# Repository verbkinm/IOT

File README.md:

<h1>IOTV</h1>
<p>
    Централизированная система управления устройствами. Под устройствами (хостами) могут подразумеваться как автономные устройства на микроконтроллерах, так и отдельные программы на компьютерах.
    Протокол для общения хоста-сервера-клиента написан на Си, так что его легко можно использовать практически на любых микроконтроллерах. На серверной части используется телеграм бот.
</p>

<p>
    Проект состоит из трёх основных частей:
<ol>
    <li>IOTV_Server.</li>
    <li>IOTV_Host.</li>
    <li>IOTV_Client.</li>
</ol>
</p>

<h2>1. IOTV_Server</h2>
<ul>
    <li>Слушает выбранный tcp порт для связи с клиентами (файл настроек).</li>
    <li>Слушает tcp и udp порты для связи с tcp/udp хостами (файл настроек). Так же возможны другие типы подключений, такие как com-порт и текствый файл.</li>
    <li>Слушает broadcast для автоматического определения tcp/udp хостов в локальной сети (файл настроек).</li>
    <li>Считывает из файла ностроек данные по хостам, к которым необходимо подключиться (адрес, порт, тип подключения и др.)</li>
</ul>

<h3>События:</h3>
<p>На сервере можно создавать события хостов следующего типа:</p>
<ul>
    <li>Подключене.</li>
    <li>Отключение.</li>
    <li>Состояние.</li>
    <li>Данные.</li>
    <li>Будильник.</li>
    <li>Таймер.</li>
</ul>

<h3>Действия:</h3>
<p>Для реагирования на события создаются действия следующих типов:</p>

<ul>
    <li><b>Data_tx</b> - отправка конкретных данных на конретное устройство.</li>
    <li><b>Data_tx_ref</b> - пересылка данных с одного устройства на другое.</li>
</ul>
<p>События и действия создаютс с помощью IOTV_Client приложения.</p>

<h2>2. IOTV_Host</h2>
<ul>
    <li><b>TCP, UDP</b> - вариант работы в режиме ожидания подключения сервера по tcp/udp порту.</li>
    <li><b>TCP_REVERSE</b> - указания хосту адреса сервера для подключения.</li>
    <li><b>Broadcast</b> - вариант broadcast рассылки для обнаружения сервером данного хоста и подключения к нему по tcp/udp порту.</li>
</ul>

<h2>3. IOTV_Client</h2>
<ul>
    <li>GUI приложение для связи с сервером. Получение данных о количестве устройств, их типе, получение/отправка данных на устройствства.</li>
    <li>Графический интерфейс разрабатывается с приоритетом использования приложения на мобильных устройствах. В первую очередь на Android смартфонах.</li>
</ul>

<h2>Конфигурационные файлы IOTV_Server</h2>

<p>
    На стороне сервера создаётся 3 .ini файла настроек:
<ul>
    <li><b>IOTV_Server.ini, секция [SERVER]:</b></li>
    <ul>
        <li><b>address</b> - ipv4 адрес, на ктором будет работать сетевая часть приложения.</li>
        <li><b>broadcastListener</b> - udp порт, на котором сервер будет слушать широковещательную рассылку от хостов.</li>
        <li><b>portClients</b> - tcp порт для подключения клиентов.</li>
        <li><b>portHosts</b> - указание tcp порта для подключения хостов <b>TCP_REVERSE</b></li>
        <li><b>client_log</b> - лог файл подключенных в данный момент клиентов.</li>
        <li><b>default_log</b> - лог файл по умолчанию. В данный файл записывается вся информация при работе программы.</li>
        <li><b>event_action_log</b> - лог файл Событий и действий.</li>
        <li><b>max_client</b> - максимальное количество одновременно подключенных клиентов.</li>
        <li><b>max_host</b> - максимальное количество одновременно подключенных хостов.</li>
    </ul>
    <br>
    <li><b>IOTV_Server.ini, секция [TG_BOT]:</b></li>
    <ul>
        <li><b>tgbot_log</b> - лог файл работы бота.</li>
        <li><b>tgbot_token</b> - токен бота.</li>
        <li><b>tgbot_trust_clients</b> - txt файл со списком id доверенных клиентов.</li>
    </ul>
</ul>
<ul>
    <li><b>IOTV_Hosts.ini</b> - файл хостов, к которым должен подключаться сервер. Описание одного хоста состоит из следующих полей:</li>
    <ul>
        <li><b>[name]</b> имя хоста. Имя в файле должно быть уникальным.</li>
        <li><b>address</b> - ipv4 адрес хоста.</li>
        <li><b>port</b>  - номер udp или tcp порта.</li>
        <li><b>connection_type</b> - тип подключения (TCP, UDP).</li>
        <li><b>interval</b> - интервал (в миллисекундах) считывания сервером данных с хоста. Минимальный интервал программно не может быть меньше 100 мс.</li>
        <li><b>logDir</b> - каталог для лог файлов данных хоста.</li>
    </ul>
</ul>
<ul>
    <li><b>IOTV_Event_Action.json</b> - файл событий и действий. Не нуждается в ручной правке. Настройка производится с IOTV_Client приложения.</li>
</ul>
</p>

<hr>

<h2>Зависимости:</h2>
<ul>
    <li>C++20.</li>
    <li>CMake.</li>
    <li>Qt 6.</li>
    <li><a href="https://github.com/reo7sp/tgbot-cpp">tgbot-cpp.</a></li>
</ul>

<h2>Сборка:</h2>

<p>
Каждый хост имеет обязательные поля:
<ul>
    <li>id устройства.</li>
    <li>имя устройства.</li>
    <li>описание устройства.</li>
</ul>
ID устройства необходимо для определение графического интерфейса на стороне клиента. Список устройств смотреть в файле <b>IOTV/docs/Список устройств.odt</b>
</p>

<p>
Каждый хост имеет два канала данных - <b>канал чтения</b> и <b>канал записи</b>. Каналы, в свою очередь, состоят из вектора блоков <b>(подканалов)</b>. Минимальное количество таких блоков - <b>0</b>, максимальное - <b>255</b>. Любой блок (подканал) должен быть одним из следующих типов:
    <ul>
        <li><b>INT_8</b> - целочисленный знаковый, 1 байт.</li>
        <li><b>INT_16</b> - целочисленный знаковый, 2 байта.</li>
        <li><b>INT_32</b> - целочисленный знаковый, 4 байта.</li>
        <li><b>INT_64</b> - целочисленный знаковый, 8 байт.</li>
        <li><b>FLOAT_32</b> - вещественный, 4 байта.</li>
        <li><b>DOUBLE_64</b> - вещественный, 8 байт. (на разных МК тип double может быть 32-битный)</li>
        <li><b>BOOL</b> - логический тип данных.</li>
        <li><b>STRING</b> - строка. Массив байт интерпретируемый как строка</li>
        <li><b>RAW</b> - Массив байт.</li>
        <li><b>NONE</b> - тип данных отсутствует.</li>
    </ul>
</p>

<h3>Примеры описывающие работу с каналами данных.</h3> 

<h3>Пример 1</h3> 

<p>Есть устройство с 3-я лампочками (реле или прочее оборудование, которое может быть в двух состояниях). На данном устройстве на канале чтения и канале записи имеется по 3 подканала. Каждый подканал имеет тип данных <b>BOOL</b>. Что бы считать данные о 1-й лампочке - необходимо получить данные с канала чтения 0-го подканала. Что бы считать данные о 2-й лампочке - необходимо получить данные с канала чтения 1-го подканала и т.д. Что бы включить 3-ю лампочку, необходимо в канал записи во 2-й подканал записать <b>true</b> или <b>1</b> и т.д:
</p>
<div>
    <div style="display: table; margin: 0 auto;">

    </div>
</div>

<h3>Пример 2</h3> 
<p>Есть устройство с 3-я датчикам (температура, влажность, давление). На данном устройстве на канале чтения имеется 3 подканала, на канале записи - 0 подканалов. Каждый подканал имеет тип данных <b>FLOAT_32</b>. Что бы считать данные температуры - необходимо получить данные с канала чтения 0-го подканала. Что бы считать данные влажности - необходимо получить данные с канала чтения 1-го подканала. Что бы считать данные давления - необходимо получить данные с канала чтения 2-го подканала:
</p>
<div>
    <div style="display: table; margin: 0 auto;">

    </div>
</div>

<h3>Пример 3</h3> 
<p>Большое количество подканалов и их разные типы можно использовать для создания более сложных решений. Как пример, онлайн камера:
</p>
<div style="width: 100%">
    <div style="display: table; margin: 0 auto;">
        
    </div>
</div>

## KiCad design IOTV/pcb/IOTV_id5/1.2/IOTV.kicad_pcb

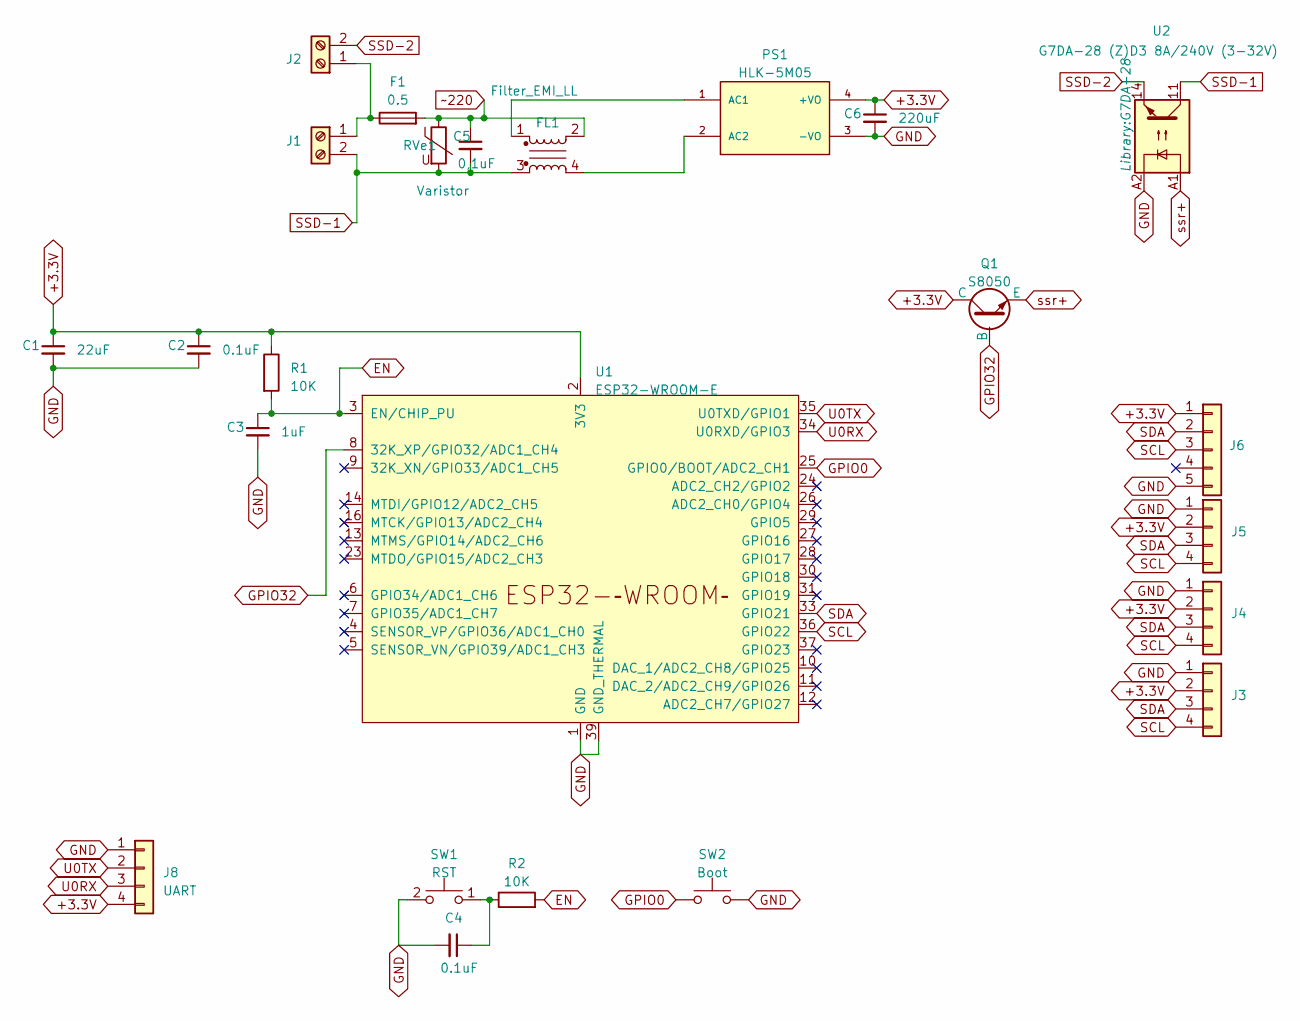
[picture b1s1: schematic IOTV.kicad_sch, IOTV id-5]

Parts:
C1, C2, C3, C4: C_Generic; C_1206_3216Metric
C5: C_Generic; C_Rect_L13.0mm_W5.0mm_P10.00mm_FKS3_FKP3_MKS4
C6: C_Generic; CP_Radial_D8.0mm_P5.00mm
F1: 0.5; Fuseholder_Cylinder-5x20mm_Schurter_0031_8201_Horizontal_Op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
FL1: Filter_EMI_LL; L_CommonMode_Toroid_Vertical_10x13mm
J1, J2: Screw_Terminal_01x02; TerminalBlock_Phoenix_MKDS-1,5-2_1x02_P5.00mm_Horizontal
J3, J4, J5: Conn_01x04; PinHeader_1x04_P2.54mm_Vertical
J6: Conn_01x05; PinHeader_1x05_P2.54mm_Vertical
J8: UART; PinHeader_1x04_P2.54mm_Vertical
PS1: HLK-5M05; CONV_HLK-5M05; PARTREV N/A
Q1: S8050; SOT-23
R1, R2: 10K; R_1206_3216Metric
RVe1: Varistor; RV_Disc_D21.5mm_W4.8mm_P10mm
SW1: RST; SW_SPST_TL3342
SW2: Boot; SW_SPST_TL3342
U1: ESP32-WROOM-E; ESP32-WROOM-32E
U2: G7DA-28 (Z)D3 8A/240V (3-32V); G7DA-28

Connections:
+3.3V: C1.1, C2.1, C6.1, J3.2, J4.2, J5.2, J6.1, J8.4, PS1.4 (+VO), Q1.3 (C), R1.1, U1.2 (3V3)
EN: C3.1, R1.2, R2.2, U1.3 (EN/CHIP_PU)
GND: C1.2, C2.2, C3.2, C4.2, C6.2, J3.1, J4.1, J5.1, J6.5, J8.1, PS1.3 (-VO), SW1.2, SW2.2, U1.1 (GND), U1.15 (GND), U1.38 (GND), U1.39 (GND_THERMAL), U2.A2
GPIO0: SW2.1, U1.25 (GPIO0/BOOT/ADC2_CH1)
GPIO32: Q1.1 (B), U1.8 (32K_XP/GPIO32/ADC1_CH4)
unnamed: C4.1, R2.1, SW1.1
unnamed: F1.1, J1.1, J2.1
unnamed: FL1.1, PS1.1 (AC1)
unnamed: FL1.4, PS1.2 (AC2)
SCL: J3.4, J4.4, J5.4, J6.3, U1.36 (GPIO22)
SDA: J3.3, J4.3, J5.3, J6.2, U1.33 (GPIO21)
SSD-1: C5.2, FL1.3, J1.2, RVe1.2, U2.11
SSD-2: J2.2, U2.14
U0RX: J8.3, U1.34 (U0RXD/GPIO3)
U0TX: J8.2, U1.35 (U0TXD/GPIO1)
ssr+: Q1.2 (E), U2.A1
~220: C5.1, F1.2, FL1.2, RVe1.1

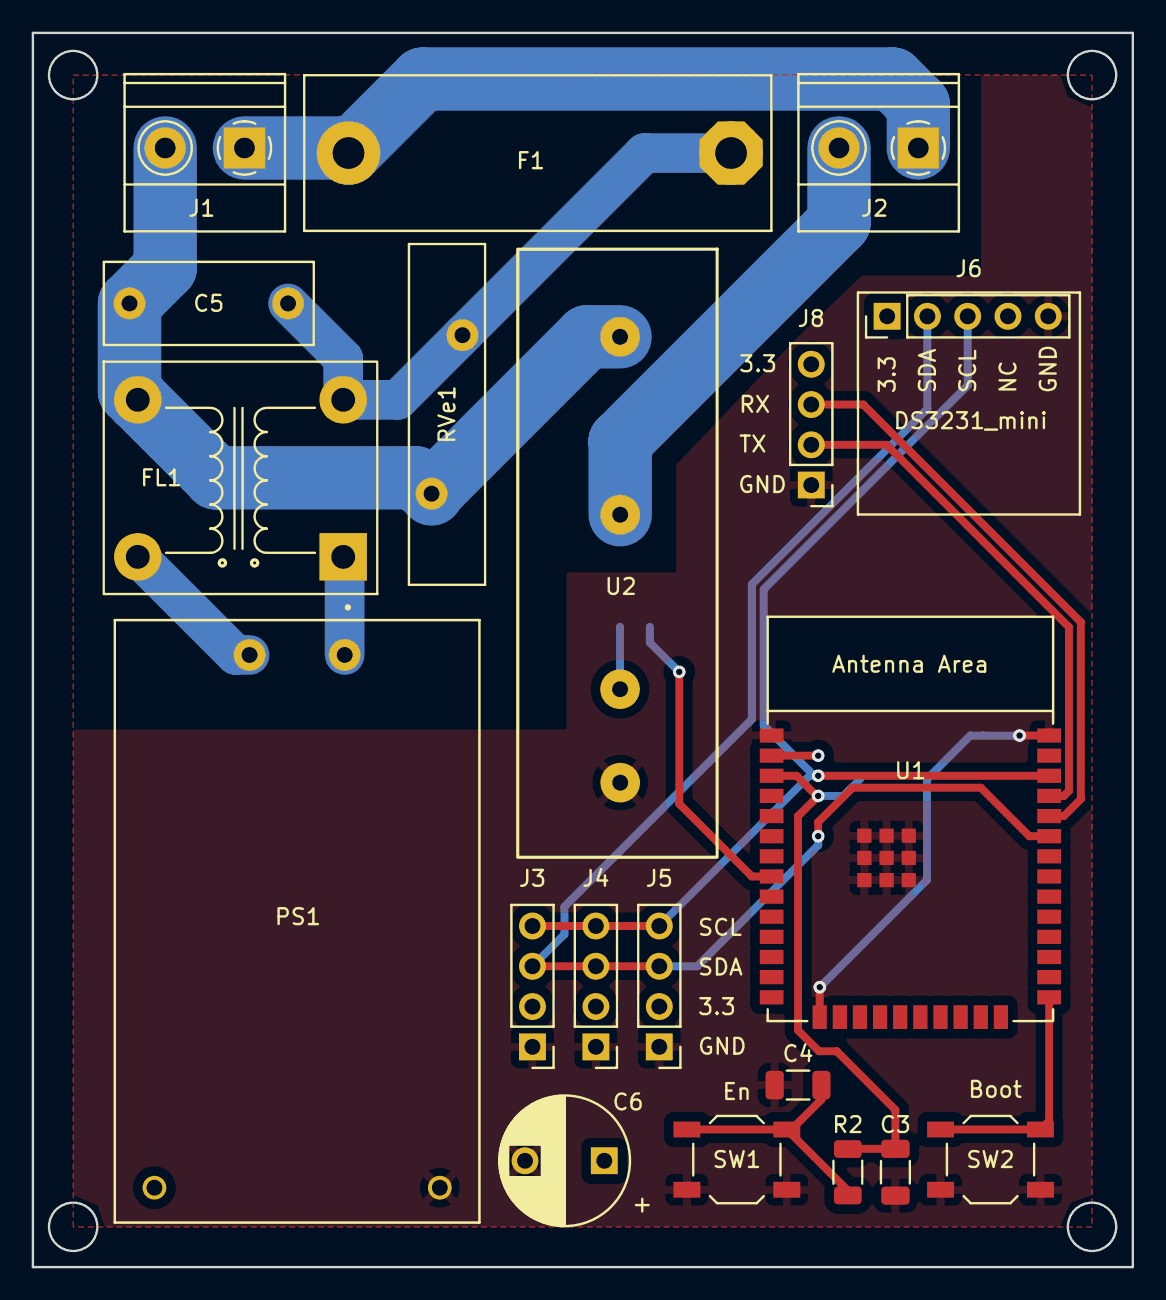
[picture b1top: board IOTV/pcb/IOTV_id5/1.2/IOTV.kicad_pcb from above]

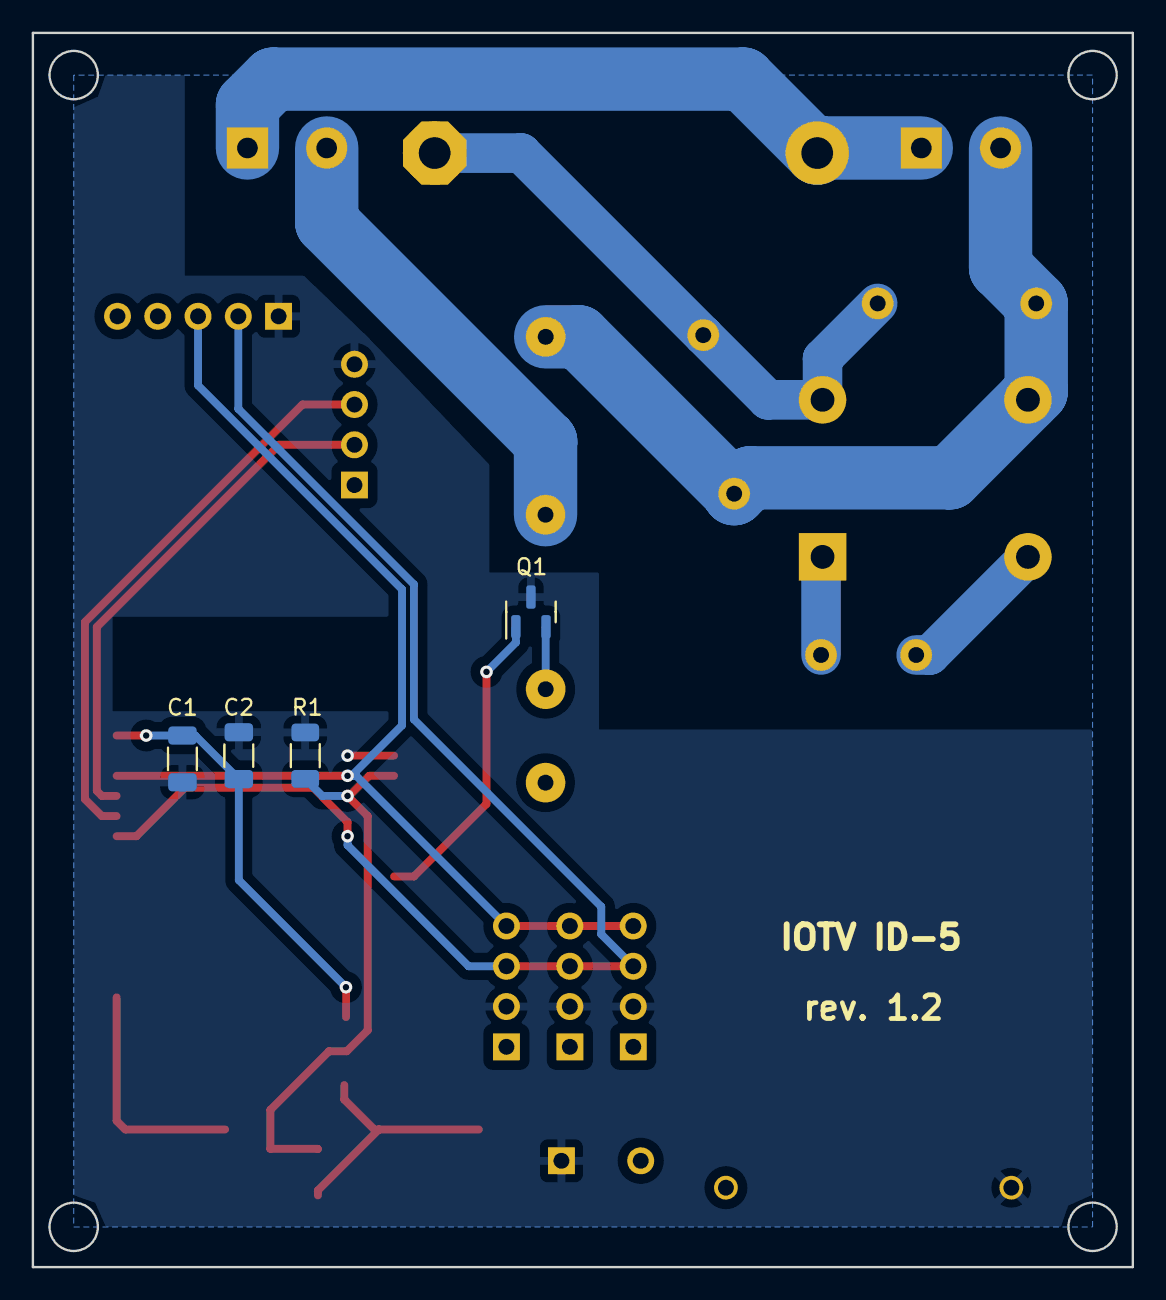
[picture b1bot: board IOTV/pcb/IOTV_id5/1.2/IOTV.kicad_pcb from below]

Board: 2 copper layers, 69.4 x 77.8 mm, 24 parts (4 on the bottom side), 17 nets.

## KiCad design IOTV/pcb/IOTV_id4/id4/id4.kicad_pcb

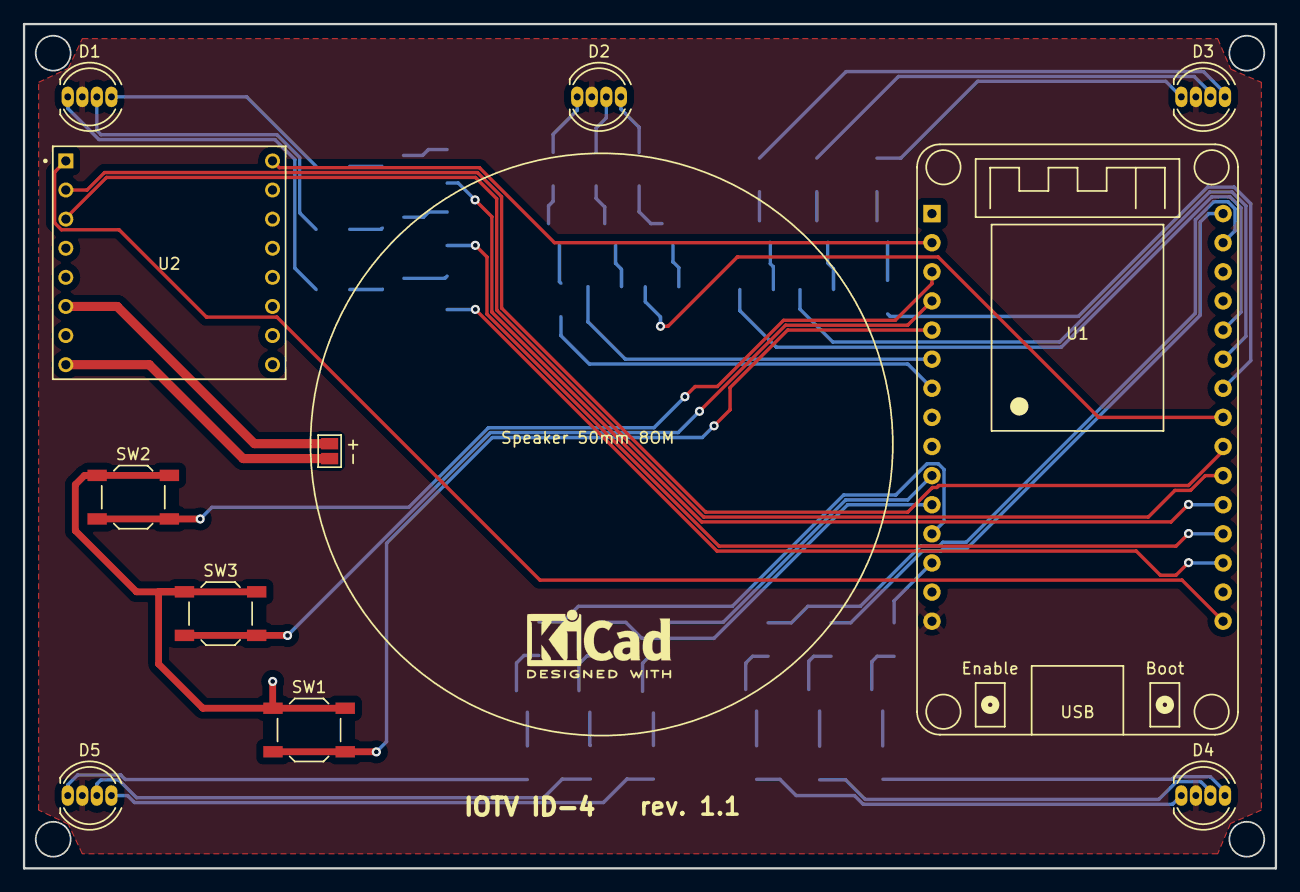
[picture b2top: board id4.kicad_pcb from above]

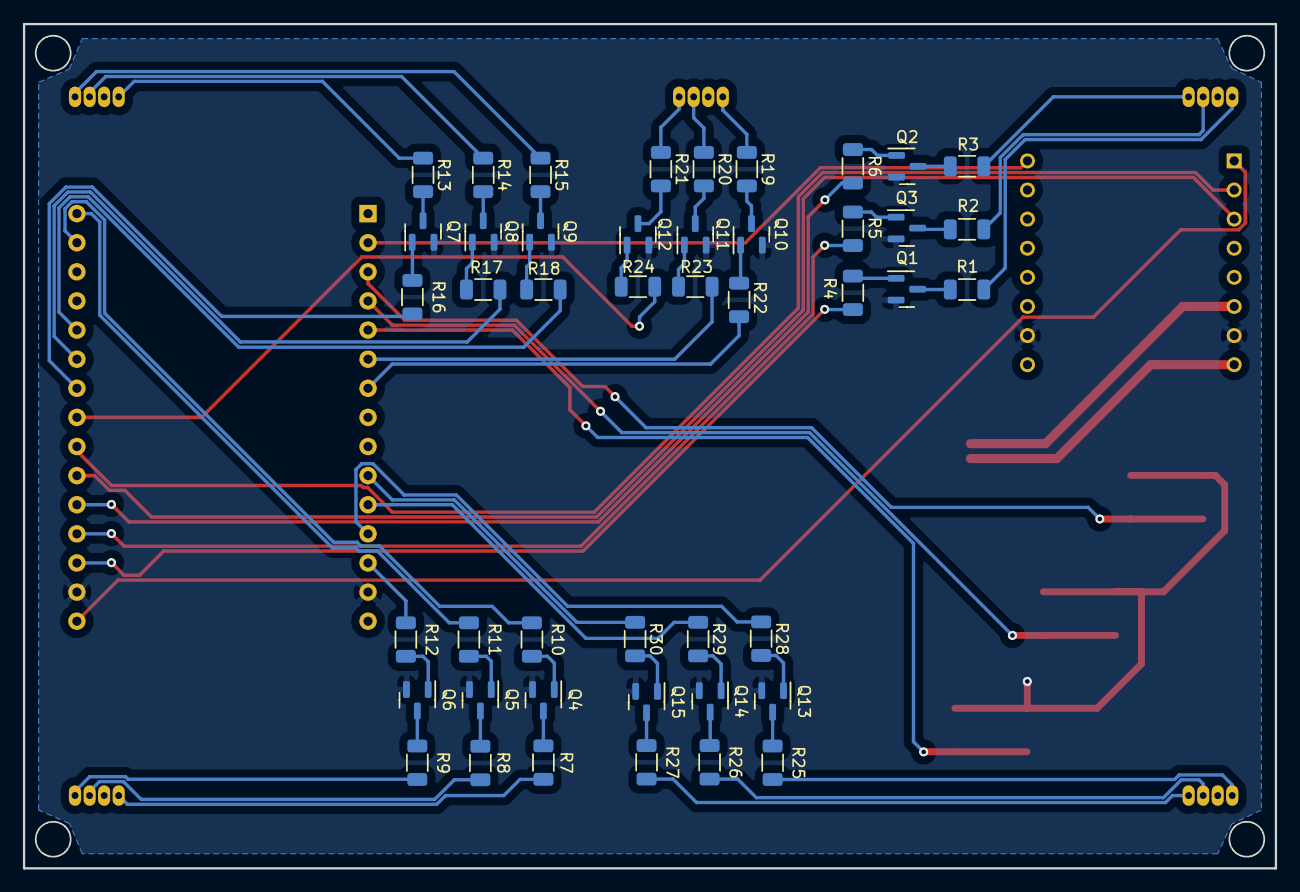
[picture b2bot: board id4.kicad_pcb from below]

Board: 2 copper layers, 109.2 x 73.7 mm, 56 parts (45 on the bottom side), 71 nets.

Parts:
D1, D2, D3, D4, D5: LED_RGBA; LED_D5.0mm-4_RGB
Q1, Q2, Q3, Q4, Q5, Q6, Q7, Q8, Q9, Q10, Q11, Q12, Q13, Q14, Q15: S8050; SOT-23
R1, R7, R13, R19, R25: 150; R_1206_3216Metric
R2, R8, R14, R20, R26: 330; R_1206_3216Metric
R3, R4, R5, R6, R9, R10, R11, R12, R15, R16, R17, R18, R21, R22, R23, R24, R27, R28, R29, R30: 100; R_1206_3216Metric
SW1, SW2, SW3: SW_Push; SW_SPST_TL3342
U1: ESP32_DevKit_V1_DOIT; esp32_devkit_v1_doit
U2: DFR0299; MODULE_DFR0299
dynamic1: Speaker; SolderJumper-2_P1.3mm_Open_Pad1.0x1.5mm

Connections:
GND: Q1.2 (E), Q2.2 (E), Q3.2 (E), Q4.2 (E), Q5.2 (E), Q6.2 (E), Q7.2 (E), Q8.2 (E), Q9.2 (E), Q10.2 (E), Q11.2 (E), Q12.2 (E), Q13.2 (E), Q14.2 (E), Q15.2 (E), SW1.1, SW2.1, SW3.1, U1.14 (GND), U1.17 (GND), U2.7 (GND), U2.10 (GND)
GPIO_2: R5.1, U1.19 (IO2)
GPIO_4: R6.1, U1.20 (IO4)
GPIO_5: R24.1, U1.23 (IO5)
GPIO_12: R28.1, U1.12 (IO12)
GPIO_13: R12.1, U1.13 (IO13)
GPIO_14: R29.1, U1.11 (IO14)
GPIO_15: R4.1, U1.18 (IO15)
GPIO_16: U1.21 (IO16), U2.3 (TX)
GPIO_17: U1.22 (IO17), U2.2 (RX)
GPIO_18: R16.1, U1.24 (IO18)
GPIO_19: R17.1, U1.25 (IO19)
GPIO_21: R18.1, U1.26 (IO21)
GPIO_22: R10.1, U1.29 (IO22)
GPIO_23: R11.1, U1.30 (IO23)
GPIO_27: R30.1, U1.10 (IO27)
GPIO_32: R23.1, U1.6 (IO32)
GPIO_33: R22.1, U1.7 (IO33)
GPIO_34: SW3.2, U1.4 (IO34)
GPIO_35: SW1.2, U1.5 (IO35)
GPIO_36: U1.2 (SENSOR_VP), U2.16 (BUSY)
GPIO_39: SW2.2, U1.3 (SENSOR_VN)
unnamed: D1.4 (BK), R3.1
unnamed: D1.3 (GK), R2.1
unnamed: D1.1 (RK), R1.1
unnamed: D2.4 (BK), R21.1
unnamed: D2.3 (GK), R20.1
unnamed: D2.1 (RK), R19.1
unnamed: D3.4 (BK), R15.1
unnamed: D3.3 (GK), R14.1
unnamed: D3.1 (RK), R13.1
unnamed: D4.4 (BK), R9.1
unnamed: D4.3 (GK), R8.1
unnamed: D4.1 (RK), R7.1
unnamed: D5.4 (BK), R27.1
unnamed: D5.3 (GK), R26.1
unnamed: D5.1 (RK), R25.1
unnamed: Q1.1 (B), R4.2
unnamed: Q1.3 (C), R1.2
unnamed: Q2.1 (B), R6.2
unnamed: Q2.3 (C), R3.2
unnamed: Q3.1 (B), R5.2
unnamed: Q3.3 (C), R2.2
unnamed: Q4.1 (B), R10.2
unnamed: Q4.3 (C), R7.2
unnamed: Q5.1 (B), R11.2
unnamed: Q5.3 (C), R8.2
unnamed: Q6.1 (B), R12.2
unnamed: Q6.3 (C), R9.2
unnamed: Q7.1 (B), R16.2
unnamed: Q7.3 (C), R13.2
unnamed: Q8.1 (B), R17.2
unnamed: Q8.3 (C), R14.2
unnamed: Q9.1 (B), R18.2
unnamed: Q9.3 (C), R15.2
unnamed: Q10.1 (B), R22.2
unnamed: Q10.3 (C), R19.2
unnamed: Q11.1 (B), R23.2
unnamed: Q11.3 (C), R20.2
unnamed: Q12.1 (B), R24.2
unnamed: Q12.3 (C), R21.2
unnamed: Q13.1 (B), R28.2
unnamed: Q13.3 (C), R25.2
unnamed: Q14.1 (B), R29.2
unnamed: Q14.3 (C), R26.2
unnamed: Q15.1 (B), R30.2
unnamed: Q15.3 (C), R27.2
unnamed: U2.6 (SPK1), dynamic1.1
unnamed: U2.8 (SPK2), dynamic1.2
VCC_3.3: U1.16 (3V3), U2.1 (VCC)
VCC_5: D1.2 (A), D2.2 (A), D3.2 (A), D4.2 (A), D5.2 (A), U1.15 (VIN)

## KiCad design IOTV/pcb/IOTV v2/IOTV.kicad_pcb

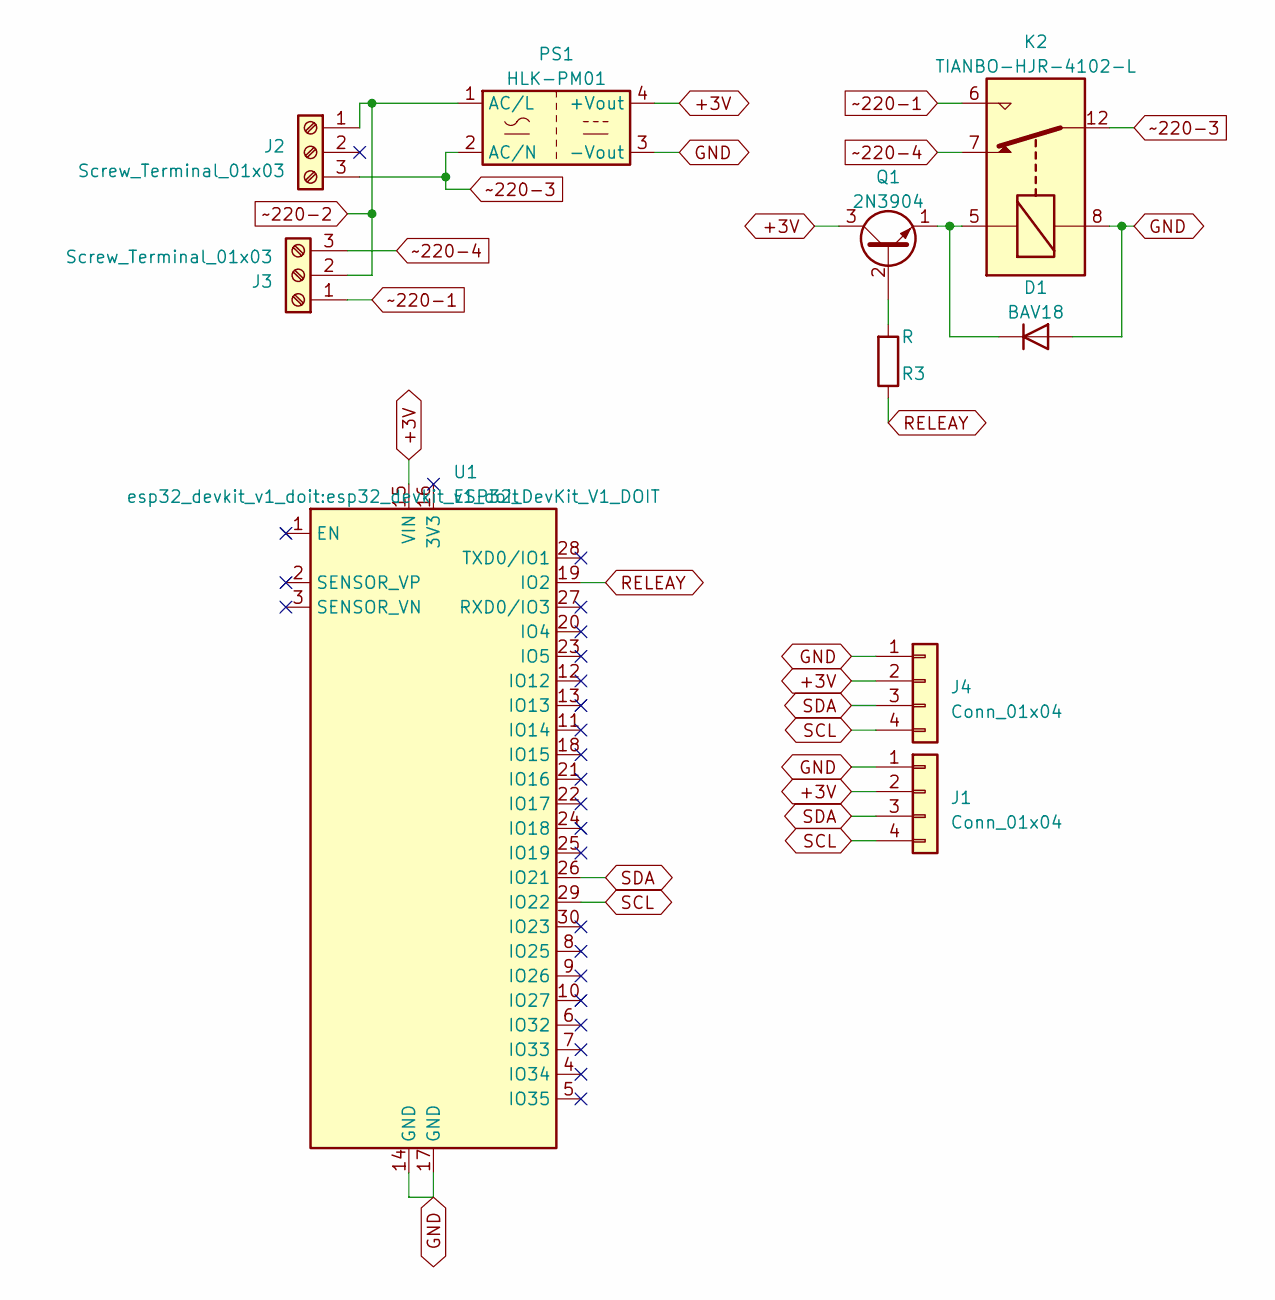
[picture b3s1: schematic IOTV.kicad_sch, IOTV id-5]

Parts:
D1: BAV18; D_DO-35_SOD27_P7.62mm_Horizontal
J1, J4: Conn_01x04; PinHeader_1x04_P2.54mm_Vertical
J2, J3: Screw_Terminal_01x03; TerminalBlock_Phoenix_MKDS-1,5-3_1x03_P5.00mm_Horizontal
K2: TIANBO-HJR-4102-L; Relay_SPDT_HJR-4102
PS1: HLK-PM01; Converter_ACDC_HiLink_HLK-PMxx
Q1: 2N3904; TO-92_Inline
R3: R; R_Axial_DIN0204_L3.6mm_D1.6mm_P1.90mm_Vertical
U1: ESP32_DevKit_V1_DOIT; esp32_devkit_v1_doit

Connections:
+3V: J1.2, J4.2, PS1.4 (+Vout), Q1.3 (C), U1.15 (VIN)
GND: D1.2 (A), J1.1, J4.1, K2.8, PS1.3 (-Vout), U1.14 (GND), U1.17 (GND)
unnamed: D1.1 (K), K2.5, Q1.1 (E)
unnamed: Q1.2 (B), R3.2
RELEAY: R3.1, U1.19 (IO2)
SCL: J1.4, J4.4, U1.29 (IO22)
SDA: J1.3, J4.3, U1.26 (IO21)
~220-1: J3.1, K2.6
~220-2: J2.1, J3.2, PS1.1 (AC/L)
~220-3: J2.3, K2.12, PS1.2 (AC/N)
~220-4: J3.3, K2.7

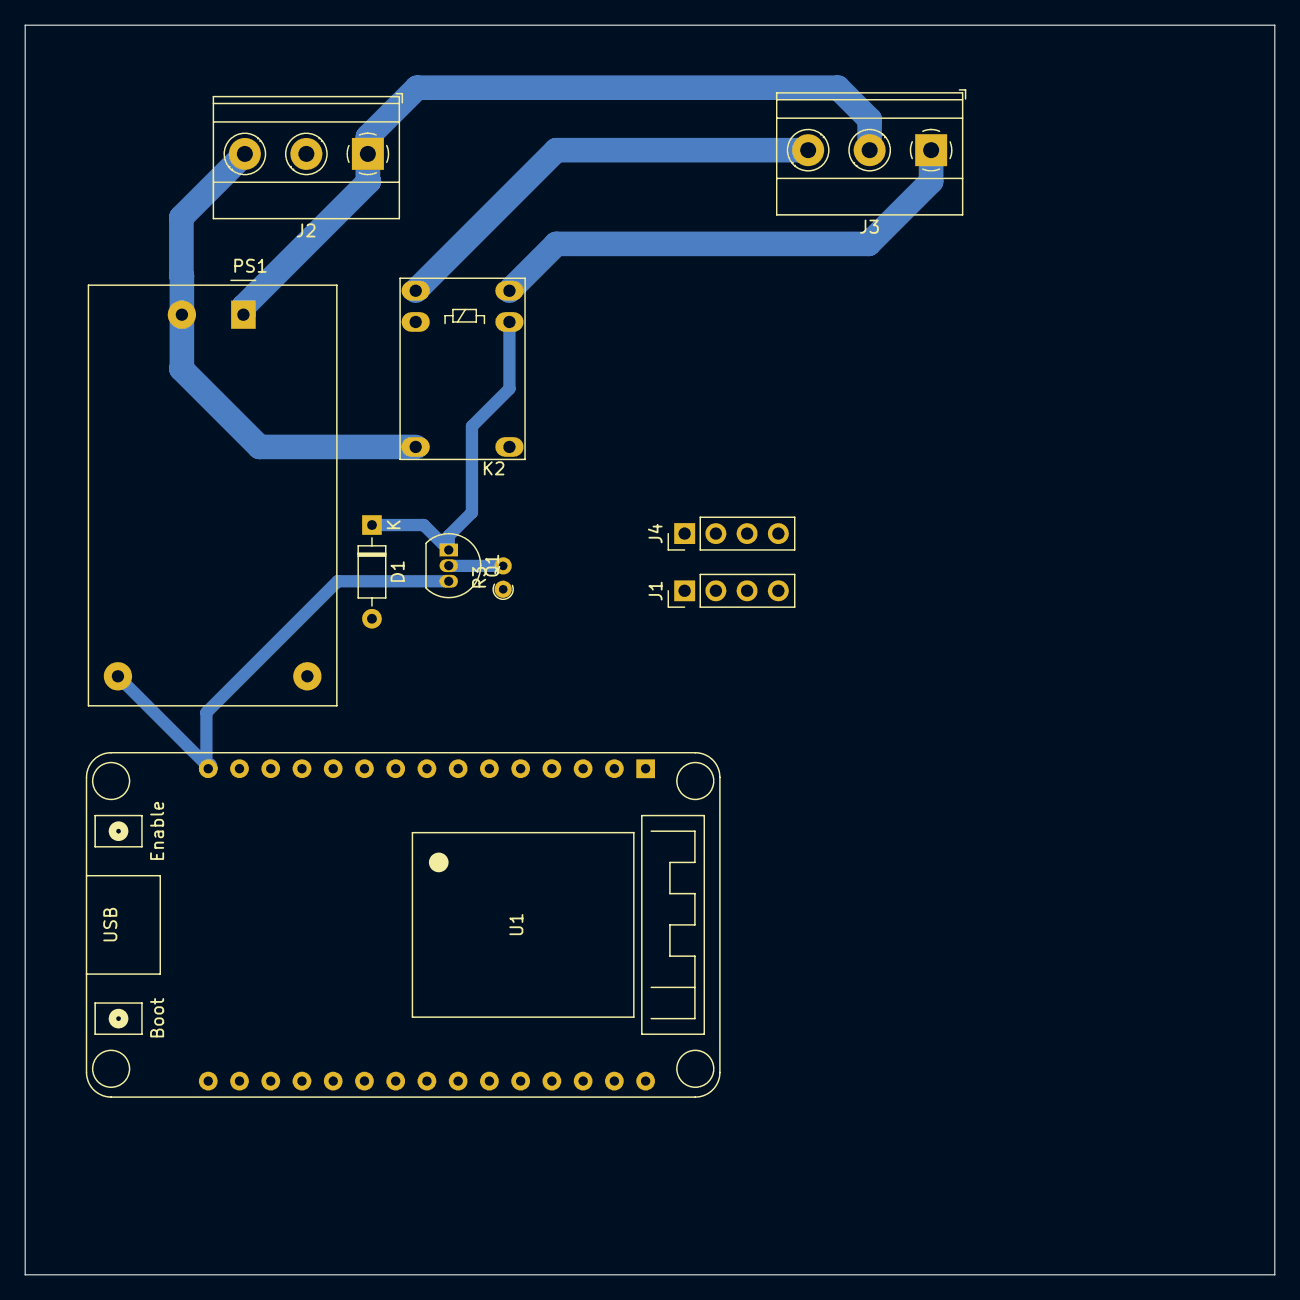
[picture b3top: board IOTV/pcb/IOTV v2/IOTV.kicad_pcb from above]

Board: 2 copper layers, 101.6 x 101.6 mm, 10 parts (0 on the bottom side), 11 nets.

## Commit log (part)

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2022-10-26 qml Home
2022-10-26 fix
    Отказ от библиотек
    Switch - время отзыва
2022-11-02 id - 4
2022-11-04 id 4
2022-11-14 id - 4
    Добавлены картинки для кнопок
2022-11-23 id -2
2022-11-23 id - 2
2022-11-23 Grid View Home Page
2022-11-24 QML_Client - перенос settings в qml
2022-11-25 Device Settings
2022-11-30 id - 4
    Fix
2023-01-02 MK fix
2023-01-02 MK
    id - 4
2023-01-09 Android manifest
2023-01-09 vl6180
2023-01-09 qml loader
2023-01-10 IOTV_Client
2023-01-17 IOTV_2
2023-01-17 IOTVP
    Разработка протокола
2023-01-17 IOTVP
2023-01-18 Test for IOTVP
2023-01-19 IOTVP_Test
2023-01-19 IOTVP_Creator
2023-01-22 IOTVP_embedded
2023-01-24 fix tests
2023-01-25 restore file
2023-01-25 restore files
2023-01-25 Time compare C++ vs C
2023-01-27 IOTV_host
2023-01-27 Собирается с новым протоколом для SH
2023-01-28 empty Protocol dir
2023-01-29 remove IOTV_SH SC
2023-01-30 IOTVP завершен
2023-01-30 remove
    isLittleEndian and dataReverse
2023-01-30 ID 1
    ESP-01_2 под IOTVP_embedded
2023-01-30 ID 4
    IOTVP_embedded
2023-01-31 Client qml
    review
2023-02-01 Client_QML
2023-02-01 Auto stash before merge of "main" and "origin/main"
2023-02-02 Client qml
2023-02-02 MK - id 4
2023-02-03 MK id 4
2023-02-06 Client_QML
    fix update from id 0
2023-02-07 IOTV_tools
    IOTVP_diagnostics
2023-02-10 Очередное ревью
2023-02-10 MK 2 fix IOTV_server fix
2023-02-11 id - 4 clearHeader id - 2 clearHeader IOTV_Client - id 4
2023-02-12 id - 2 id - 4 iot_host ping state counters
2023-02-12 timer state
2023-02-13 IOTV_tools
    конвертер - ok
2023-02-13 review
2023-02-13 MakeFile ignore
2023-02-14 IOTV_Client
    device[name].update()
2023-02-15 IOTV_Client
    Notification
2023-02-15 IOTV_Client
    Loader
2023-02-16 loader
2023-02-17 IOTV_Client
    review. Много loader стало и мало js
2023-02-19 Много чего =)
2023-02-23 review all
2023-03-05 stash
2023-03-05 Исправлен баг с потоками для хостов и клиентов
2023-03-05 server 0.5
2023-03-10 id 1 + id 4
2023-03-21 id-1 ESP32
2023-04-14 iotvp - переписано на Си.
    Добавлен id-1 для esp32 на freeRTOS
2023-04-18 id-5
2023-04-21 Документация
2023-05-02 docs
2023-05-10 ds3231
2023-05-10 IOTV_Client 0.6.5
2023-05-11 IOTV_Client_QML id-5
2023-05-12 qml id5
2023-05-12 qml 0.6.6
2023-05-16 IOTV_server 0.6
    Добавлена поддержка UDP
2023-05-19 Events
    Начало разработки событий
2023-05-20 Raw
    Добавление операторов сравнения и арифметический операторов. Добавление тестов по этой части
2023-05-20 IOTV_ACTION_DATA_TX_REF
2023-05-22 pcb id4
2023-05-22 merge
2023-05-23 Расширение протокола
2023-05-23 доработка протокола
    У Header убраны указатели данных, оставлен один - void *
2023-05-24 cppcheck
2023-05-24 json parse event action
2023-05-26 pcd id5
2023-05-29 parse json Event action
2023-05-29 create Event_Action_Parser class
2023-05-29 Список событий и действий в json формат
2023-05-29 id-5 pcb
2023-05-30 Action parse to json format
2023-05-30 qml events
2023-05-30 test
2023-05-31 активити с созданием нового события
2023-06-01 протокол, добавлен тип tech
    передача json event action от сервера к клиенту
2023-06-01 qml icons
2023-06-01 qml fix
2023-06-05 Raw, eventManager fix
2023-06-07 MK id5
2023-06-09 parse json in qml client
2023-06-10 cad корпус id5
2023-06-12 cad id5
2023-06-15 json parse
2023-06-16 qml client
    actions
2023-06-16 qml client
2023-06-22 pcb src id4
2023-06-25 Auto stash before merge of "dev2" and "origin/dev2"
2023-06-25 MK id4
2023-06-26 MK, docs id4
2023-07-07 id4
    pcd docs MK
2023-07-10 iotv server
    проверка существования IOTV_Event_Action.json файла и его создание при отсутствии
2023-07-10 iotv client
    spacing для создания событий
2023-07-12 EVENT ACTION JSOn
    Запись и удаление событий с клиента
2023-07-12 iotv client
2023-07-13 iotv 0.7
2023-07-16 много всего для iotv client
2023-07-17 IOTV_client id_4
2023-07-18 id_4 iotvClient
2023-07-21 iotv client id4
2023-07-21 iotv clietn id4
2023-07-23 ITOV id4, iotv server
2023-07-24 iotv MK id4
2023-07-26 PCB - ID4
2023-07-27 id4 cad
2023-07-28 cad id4
2023-07-31 id4 pcd cad
2023-08-01 cad id4.1
2023-08-01 IOTV_Server при запуске с параметрами по умолчанию грузит CPU
2023-08-02 cad id4 рисунки на кнопках
2023-08-02 pcb id4 - rezonit OK
2023-08-03 review server + восстановление тестов
2023-08-03 Тесты восстановлены
2023-08-05 pcb id5 маркировки номиналов резисторов
2023-08-09 MK ID5 ver 1.1
2023-08-10 MK ID5 ver 1.1
    boot screen
2023-08-10 pcd id 4
    на кнопках исправлен контакт с 5в на 3,3в
2023-08-14 PCB id5
2023-08-14 pcb id5 rev1.2
2023-08-15 pcb id5 rev 1.2
2023-08-15 pcb id5 rev 1.1 and rev 1.2
2023-08-31 pcb id5 rev 1.2 ssr
2023-09-14 MK id5 1.1
2023-09-18 id5 время и дата выравнивание по центру
2023-09-25 iotvClient
2023-09-28 Прошивка по умолчанию.
2023-09-29 IOTV Factory - ok
2023-10-02 PCB id4 кнопки на землю
2023-10-06 ID 7 описание
2023-10-13 передача потоковых данных
2023-10-16 потоки чтения и записи
2023-10-16 потоки
2023-10-16 изменение протокола. Разработка версии 3
2023-10-17 передача фрагментами
2023-10-18 передача фрагментов до клиента
2023-10-19 Qimage online id8
2023-10-20 id8 Qimage online
2023-10-23 server, client - 0.8 - OK
2023-10-27 videoFrame
2023-11-13 Wrap_QByteArray
    передача qbytearray C++ -> qml -> C++
2023-12-01 rgb_panel
2023-12-01 rgb panel
2023-12-09 rgb panel
    panel status
2023-12-11 rgb panel
    json
2023-12-13 rgb panel
    wifi autoconnect
2023-12-18 rgb panel sntp - ok
2023-12-22 rgb panel
    Основное окно - шаблон данных
2023-12-26 rgb panel
    настройки дисплея - ok
2023-12-26 rgb panel
    Русская раскладка клавиатуры
2023-12-27 rgb panel
    дневной/ночной режимы яркости дисплея
2023-12-27 rgb panel
    Сообщение при ошибки SD карты
2023-12-28 rgb panel
    Установка времени/даты вручную. Погода за неделю.
2023-12-29 rgb panel
    утечка памяти для service weather исправлена
2024-01-16 rgb panel
    График погоды - ok
2024-01-17 rgb panel
    удалены extern для переменных-регистров статусов и ошибок
2024-01-19 id8 esp32-cam
2024-01-19 IOTV server
    _counterPing и _counterState убрано с лишних мест
2024-01-22 IOTV_Client id8
2024-01-22 IOTV client
    id 8 - звук отстаёт!
2024-01-24 meteo_home_II
2024-01-25 home_meteo_II
2024-01-26 home_meteo_II fix
2024-01-29 home_meteo_II
    Оповещение о новых обновлениях
2024-01-30 home_meteo_II
    Заставка запуска
2024-02-02 home_meteo_II 0.2.1
2024-02-06 home_meteo_II 0.2.2
    bme280
2024-02-09 home_meteo_II 0.3.0 настройка для калибровки bme280
2024-02-09 home_meteo_II 0.3.1 DS3231 синхронизация при запуске
2024-02-09 home_meteo_II 0.3.1 fix
2024-02-12 iotv client id8
2024-02-14 home_meteo_II 0.3.2
    калибровка датчика bme280 по 0,1%.
    на главном экране у каждого блока своя частота обновления информации.
    в настройках датчиков экран gui не тормозит из-за ошибок считывания bme280
2024-02-16 home_meteo_II 0.4.0
    Добавлена страница "Погода в доме" с локальными показаниями температуры, влажности и давления
2024-02-19 home_meteo_II 0.4.1
    Поворот дисплея до стартовой заставки.
2024-02-21 broadcast
2024-02-21 IOTV_Server fix server
2024-02-21 IOTV_CLIENT fix producer
2024-02-21 Сервер и клиент - 0.9
2024-02-22 IOTV_Server fix
2024-03-03 id_8 автообновление
2024-03-07 id5 dev
2024-03-07 MK id5 2.0.1
2024-03-13 (no branch):
    MK id5 2.3.1
2024-03-13 MK id5 2.3.1
2024-03-18 IOTV_Client SwipeView
2024-03-19 IOTV_Client изменение архитектуры
2024-03-19 IOTV_Client 0.11
2024-03-19 IOTV_Client multieffect
2024-03-21 IOTV_Client 0.12 IOTV_Server 0.10
2024-03-21 IOTV_Client 0.12 IOTV_Server 0.10 02570c
2024-03-21 TCP_reverse host connect
2024-03-22 IOTV_host_camera_udp
    Через broadcast указывается хосты как tcp так и udp
2024-03-22 IOTV_Client
    графическое представление событий
2024-03-25 IOTV_Client 0.13
    Изменены в событиях кнопки сохранить, удалить, настроить (будильник, таймер)
2024-03-25 readme
2024-03-25 IOTV_server
    UDP reverse
2024-03-26 удаление старых файлов
2024-03-26 удаление лишних файлов
2024-03-27 IOTV_server 0.11
2024-03-27 IOTV_Server 0.11.1
2024-03-28 Протокол - добавление типа Log_Data
2024-03-29 IOTV протокол - доработан запрос логов
2024-03-29 Log_Data
2024-03-30 IOTV_Client Log_Data нулевой завершающий пакет
2024-04-01 IOTV_Client charts log data id_2
2024-04-02 IOTV_Client log_data
2024-04-03 IOTV_Client 0.15
2024-04-04 Log_Data_Buff stop
2024-04-04 chartView проверка на тип данных. Отображение bool типа как 0 или 1
2024-04-05 Передача лог данных пакетами
2024-04-05 уменьшение точек на графике лога по оси X за счет округления до 0,001
2024-04-05 уменьшение точек на графике лога по оси X
    за счет отбрасывания промежуточных повторяющихся значений на осиY
    11122333456 -> 112233456
2024-04-08 IOTV_Client 0.16.3
2024-04-08 Log_Charts id5
2024-04-09 Ускорение отрисовки графика логов!
2024-04-09 log chart легенда
2024-04-10 0.16.4
2024-04-10 log chart id2
    Масштабирование и перемещение
2024-04-11 IOTV_server
    log_data парсинг лог файла в разных потоках для каждого запроса.
2024-04-11 thread_pool
2024-04-12 полная херня с потоками!
2024-04-12 потоки - deleteLater
2024-04-13 streamread исправлена ошибка взаимодействия между потоками
2024-04-15 MK id5
    Удалена работа с ds3231
2024-04-15 Log_chart - интервалы для каналов
2024-04-16 0.17
    масштабирования по осям. Запросы данных только для отображаемых lineSeries
2024-04-30 логи по хостам записываются отдельно для каждого канала
2024-05-08 MK id_2
2024-05-16 Документация устройств - ID9
2024-05-17 документация dht22
2024-05-17 документация ID9
2024-05-22 extern C для кода протокола IOTVP
2024-05-29 iotv_server 0.16
    имя iotv_host устанавливается из пакета identification поля name. Одинаковые имена исключаются. К имени добавляется номер, если оно повторяется.
2024-05-30 MK id5 2.4.3
2024-05-30 iotv_server 0.17
2024-06-02 raii_iot raii_header
2024-06-03 iotv_server 0.18
2024-06-07 Переработка json событий
2024-06-09 json event action
2024-06-13 json event action beta
2024-06-13 iotv_server 0.19, iotv_client 0.19
2024-06-14 iotv_client убрал alias имена устройств
2024-06-19 fatal error
2024-06-20 iotv_сервер на cmake телеграм бот
2024-06-20 Eraser_iotv
2024-06-20 Config_Server
2024-06-20 iotv_client 0.20
2024-06-20 команды бота
2024-06-20 gitignore
2024-06-20 iotv_client 0.21
2024-06-20 iotv_client 0.22
2024-06-26 удаление pcb
    удаление pcb
2024-06-29 iotv_server 0.20 fix
2024-06-29 iotv_client 0.23
2024-07-18 iotv_server 0.21
2024-07-20 iotv_client
    запуск action с клиента
2024-07-20 iotv_client и iotv_server
    запуск действия с клиента
2024-07-22 iotv_server 0.22 iotv_client 0.24
    Запуск событий и действий с клиента
2024-07-22 gradle.property
2024-07-22 iotv_client 0.25
    BUFSIZE установлен в 8192 в client.cpp. На arm по умолчанию он был равен 1024, из-за чего не отрабатывал правильно протокол iotv
2024-07-22 todo.txt
2024-07-23 iotvp, iotv_server 0.23, iotv_client 0.26
    Все response функции используют указатель на функцию записи данных
    Только responseState остался без возможности фрагментации данных
2024-07-23 iotvp
    добавлен RETURN_WARNING
    исправлен todo.txt
2024-07-24 iotvp, iotv_server 0.23, iotv_client 0.26
    Фрагментация пакета идентификации. Сборка фрагментов в один пакет при приёме.
2024-07-24 Сборщик пакетных фрагментов
2024-07-25 iotv_server 0.24, iotv_client 0.27
2024-07-25 MK id_5 2.4.3 обновление протокола
2024-07-26 protocol fix
2024-07-26 iotv_server
    Вывод информации о хостах в файл в режиме реального времени.
2024-07-27 iotv_server
    вывод данных о хостах в файлы
2024-07-31 MK id-1
2024-08-02 MK Factory_IOTV
2024-08-09 file:///home/user/eclipse-workspace/Factory_IOTV/main file:///home/user/eclipse-workspace/Factory_IOTV/CMakeLists.txt file:///home/user/eclipse-workspace/Factory_IOTV/nvs.csv file:///home/user/eclips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
2024-08-12 MK Factory_IOTV 0.1
